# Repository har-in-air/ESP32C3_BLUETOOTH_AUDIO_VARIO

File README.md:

# ESP32C3_BLUETOOTH_AUDIO_VARIO

 * Accurate, zero-lag audio variometer using Kalman filter fusion of accelerometer and pressure sensor data. 
 This project uses the [KF4D kalman filter algorithm](https://github.com/har-in-air/ESP32_IMU_BARO_GPS_VARIO/blob/master/offline/kf/compare_kf2_kf3_kf4.ipynb).

* WiFi Vario configuration via web page.
* Bluetooth LE transmission of [$LK8EX1 sentences](https://github.com/LK8000/LK8000/blob/master/Docs/LK8EX1.txt), to provide apps like [XCTrack](https://xctrack.org/) with 
accurate barometric pressure altitude and climb-rate data.
* Soft-switched power on/off.
* 'No activity' time-out power down  to conserve battery life.
* WiFi Over-the-air (OTA) firmware updates.
* [2-layer PCB layout available, sized for standard Hammond 1551K enclosure](https://github.com/har-in-air/VhARIO-ESPC3).

# Software Build Environment 
* Ubuntu 24.04 LTS AMDx64
* [Visual Studio Code with PlatformIO plugin using Arduino framework](https://randomnerdtutorials.com/vs-code-platformio-ide-esp32-esp8266-arduino/) 
* The file `platformio.ini` specifies the framework packages, toolchain and libraries used by the project. 
* LittleFS partition for hosting HTML web page content.
* Since release v1.20, the software only supports PCB layout revision B.

# Hardware

* AI-Thinker ESP-C3-12F C3FN4 module (4MByte flash, Wi-Fi and Bluetooth LE)
* CJMCU-117 module with MPU9250 9-DOF IMU and MS5611 barometric pressure sensor
* TLV75533 LDO regulator, max current 500mA
* KPEG006 broadband-audio piezo transducer
* 74HC240 used as a push-pull piezo driver for louder volume 
* MCP73871 Li-poly battery charger, max 500mA charging current
* 1800mAHr Lipoly battery
* The USB C interface supports Li-Poly battery charging and program flash/debug.

## Current Drain

With Bluetooth LE disabled, current drain is ~30mA.

With Bluetooth LE enabled and transmitting LK8EX1 messages at 10Hz, current drain is ~85mA.

# Software Build Notes

## Build Steps

* The first time you flash the ESP32-C3 with this project code, select `PROJECT TASKS -> esp32c3 -> Platform -> Erase Flash`. This will wipe the entire flash including any previous partition tables. 
* Next, select `Platform -> Build Filesystem Image`. This will build a LittleFS flash partition with the contents of the `/data` directory. The `/data` directory contains the static HTML and CSS files for the WiFi server webpage.
* Ensure the vario is switched off. 
* Connect the USB cable from your PC to the vario. 
* Press and hold the `PCCA (SW4)` button. 
* Close the jumper or slide-switch (`JP1/SW2)` depending on which part you have installed. 
* Release the `PCCA (SW4)` button. 
* You will see the USB serial/jtag port show up as a new serial port. On Ubuntu it will be `/dev/ttyACMx` instead of `/dev/ttyUSBx`. Set this new port as the upload and monitor port in platformio.ini.
* Next, select `Platform -> Upload Filesystem Image`. This will flash the LittleFS data partition to the ESP32-C3.
* Next, select `General -> Clean All`, then `Build`. This is only required once, to download the source code for the dependent libraries and build them. 
* If the libraries have already been downloaded and compiled, select `General -> Clean` to re-build only the project application code.
* Select `Build` to compile the application firmware binary. 
* Open the jumper/slide switch (`JP1/SW2`) to remove power. 
* Repeat the earlier steps with `PCCA (SW4)` and the jumper/slide switch  (`JP1/SW2`) to set up for flashing the application firmware.
* Select `Upload` to flash the application firmware binary.
* To see  serial debug prints and prompts on boot, open the  jumper/slide switch (`JP1/SW2`) to remove power. 
* Select `Monitor` in Visual Studio Code and then switch on the vario using the `PWR (SW3)` button. Note that the
serial port may change from the one used for upload e.g. from `ttyACM0` to `ttyACM1`.  

* After a full chip erase and firmware upload, there is no calibration data. So you will see a calibration error message. Follow the prompts to calibrate both accelerometer and gyroscope. Once complete, the calibration parameters will be saved to flash.
* [Example startup serial monitor output example after a full flash erase and build.](docs/first_boot_log.txt) 
* Example serial terminal output for normal vario boot (post-caliibration) : 

```
ESP-ROM:esp32c3-api1-20210207
Build:Feb  7 2021
ESP-ROM:esp32c3-api1-20210207
Build:Feb  7 2021
rst:0x15 (USB_UART_CHIP_RESET),boot:0xc (SPI_FAST_FLASH_BOOT)
Saved PC:0x42083766
SPIWP:0xee
mode:DIO, clock div:2
load:0x3fcd5810,len:0x438
load:0x403cc710,len:0x90c
load:0x403ce710,len:0x2624
entry 0x403cc710
E (236) esp_core_dump_flash: No core dump partition found!
E (236) esp_core_dump_flash: No core dump partition found!

ESP32-C3 BLUETOOTH VARIO compiled on Apr  8 2025 at 15:48:49
Firmware Revision 1.01

Load non-volatile configuration and calibration data from flash
WiFi AP credentials
SSID = 
VARIO
climbThresholdCps = 50
zeroThresholdCps = 5
sinkThresholdCps = -250
crossoverCps = 400
KALMAN FILTER
accelVariance = 100
adapt = 100
MISCELLANEOUS
pwrOffTimeoutMinutes = 10
bleEnable = true
Calibration Values
axBias = -390
ayBias = -182
azBias = 234
gxBias = 17
gyBias = -7
gzBias = 22
To start web configuration mode, press and hold the PCC button
until you hear a low-frequency tone. Then release the button
8
7
6
5
4
3
CPU Freq = 80 MHz
XTAL Freq = 40 MHz
APB Freq = 80000000 Hz
Vario mode

Audio indication of battery voltage

Battery voltage = 4.13V
E (4666) ledc: ledc_get_duty(745): LEDC is not initialized

Check communication with MS5611
crcPROM = 0x9, crc calculated = 0x9
MS5611 OK

Check communication with MPU9250
MPU9250 ID = 71, expected 0x71
MPU9250 OK
Counting down to gyro calibration
Press the PCCA button to enforce accelerometer calibration first
10
9
8
7
6
5
4
3
2
1

Calibrating gyro
Num Tries = 1
gxBias = 18
gyBias = -7
gzBias = 22
Gyro calibration OK

MS5611 config
MS5611 Calibration Coeffs : 48939 50595 29263 26380 30963 26826
Tavg : 35C
Pavg : 90986Pa
Zavg : 89864cm

KalmanFilter config
climbToneCps = 50
zeroesToneCps = 5
sinkToneCps = -250
crossoverCps = 400

Bluetooth LE LK8EX1 messages @ 10Hz

```
* The gyroscope is re-calibrated each time on power-up. You should leave the vario un-disturbed (in any orientation) when you hear the count-down beeps for gyroscope calibration. If the vario is disturbed during the gyro calibration process (e.g. you switched the vario on during flight), it will use the last saved gyro calibration parameters.

# WiFi Configuration

To put the vario into WiFi AP server mode, switch on the vario and immediately press and hold the `PCCA (SW4)` button. When you hear a confirmation tone, release the button. 

Connect to the WiFi Access Point `Vario-AP`, no password needed. 

Open the url `http://192.168.4.1` in a browser.
You can use `http://vario.local` with any OS that has mDNS support. MacOS has built-in support. For Ubuntu, install Avahi. For Windows, install Bonjour.

## Configuration Options

### WiFi Credentials
Enter your home WiFi Access Point SSID and password so that the vario can connect to the access point as a station. Then you can just enter the webpage url `http://vario.local` to access the vario configuration web page.

If the external Access Point is not configured or the configured access point is not available, e.g. on the launch site, the vario will configure itself as a standalone Wifi Access Point with SSID `Vario-AP`, no password. You can use your phone or tablet to connect first to this access point. Then access the webpage url `http://vario.local` as before.

### Audio Tone configuration

The climb tone threshold should be configured for what you consider the minimum climbrate that you can turn in without losing height. The range is +20cm/s to +100cm/s.

Since a paraglider has a 'hands-up' sink rate of approximately -1m/s in still air, anything more than this indicates rising air. 
The zero tone is used to indicate air that is rising, but not strong enough for aggressive turns. The range is -20cm/s to +20cm/s. 

The sink tone is used to indicate sinking air, not a sinking glider. The range is -400cm/s to -100cm/s.

Note that these thresholds are purely personal choices, depending on how 'talkative' you want the vario to be.

The crossover climbrate is used to adjust the frequency discrimination. The vario allocates 3 octaves of audio bandwidth to climbrates below this threshold, and 1 octave
above the threshold. So if the expected average thermal strength is +5m/s, set the threshold to 500.

### Kalman Filter configuration
Set the `variance` parameter lower for conditions with soft, wide and smooth-edged thermals. Set the parameter higher for conditions with strong, narrow and hard-edged thermals.

The `adapt` parameter will probably be removed after flight trials. Higher values add more uncertainty into the Kalman filter so it can respond to high acceleration transitions quickly, while maintaining a high degree of damping in zero acceleration conditions.

### Inactivity Time-out
The vario will power off automatically to save battery life if it does not detect climb/sink rates beyond a minimum threshold within a specified interval (specified in minutes). If you often stand on the launch site for several minutes, hooked-up to the glider and waiting for launch conditions to improve, use a larger time-out.

### Bluetooth LK8EX1
If you enable this option, the vario will transmit $LK8EX1 sentences using the Bluetooth LE protocol at 10Hz. The Bluetooth device name is `BLE-Vario`.

`XCDisplay` app on Apple iPhone connected to the vario, displaying pressure altitude and climbrate.

# Usage

## Power On 
To power on, press the `PWR (SW3)` button and hold (~1 second) until you see the power/bluetooth LED turn on. Release.

The vario will first indicate the battery charge status with a series of long beeps. 5 beeps for fully charged, 1 beep for discharged.

After a pause, the vario will indicate the countdown to gyro calibration with a series of 10 shorter beeps. You should ensure the vario is left undisturbed, in any orientation (do not hold it in your hand). At the end of the countdown and a brief pause, you may hear an initial squawk as the filter initializes, but it should settle down in a few seconds. Now the vario is operational and providing audio feedback.

If you want to force accelerometer re-calibration, press the `PCCA (SW4)` button during the gyro calibration countdown. Now the vario will start a 50 short beep countdown at a fast rate. At this point you should place the vario flat on a horizontal surface (confirm with a bubble level if possible) without any disturbance, vibrations etc. Do not hold or press down on the vario case. At the end of the 50 beeps, the accelerometer will be calibrated, and then the countdown to gyro calibration will start.

### Power/Bluetooth LED
If Bluetooth transmission is disabled, the power/bluetooth LED will stay on.

If Bluetooth transmission is enabled, the power/bluetooth LED will start blinking once every 2 seconds after transmission starts.

### Audio Mute 
When the vario has finished initialization and is providing vario audio feedback, a brief press of the `PCCA (SW4)` button  will toggle the audio on / off.

This is convenient if you have set the zero-tone threshold to a negative value or close to zero and don't want the distraction of a beeping vario while you are hooked in to the glider and waiting to launch.

## Power Off
To power off, press the `PWR (SW3)` button and hold (~2 seconds) until you hear a confirmation audio tone. If the power/bluetooth LED was on, it will turn off as well. Release.

# Notes on Calibration and Use
The accelerometer offset calibration with the vario in a horizontal position needs to be done AFTER the board is installed in the case and BEFORE first use.

Gyro offset calibration is done on each power up. For that the only requirement is that the unit should not be disturbed, it can be in any orientation.  If it is disturbed, it will use the previous saved gyro offsets. This will not be an issue  if you successfully calibrated the gyro in the past few days and are flying in similar temperature conditions.

After offset calibration and in normal use the AHRS software computes the vario orientation in Earth coordinates and then the 
net acceleration along the Earth coordinates +Z axis, every 2mS. This is NOT the IMU chip z axis acceleration. 

So the vario does not have to be horizontal during use, you can mount it to your waist strap or riser.

You will need to redo the accelerometer offset calibration if you have reinstalled the board in the case, or tightened/loosened the mounting screws. The stress from the mounting screws will translate to stress on the MEMS structures in the IMU chip soldered to the module board, which will change the axis offsets. 

My friend who mounted the module board with a standard 0.1in header to the main PCB had very large accelerometer offsets. I was concerned that he had a defective MPU9250 chip. He reinstalled the IMU module board with double-sided foam tape and thin flexible wires, and then the offsets on all axes were very low.

The accelerometer calibration will remove the offsets, but it's good to remove external contributing factors, especially if the offset is so large that it affects the dynamic range. 

# Credits

Prototype design, component sourcing, PCB assembly and testing in collaboration with Benoit Arnal.

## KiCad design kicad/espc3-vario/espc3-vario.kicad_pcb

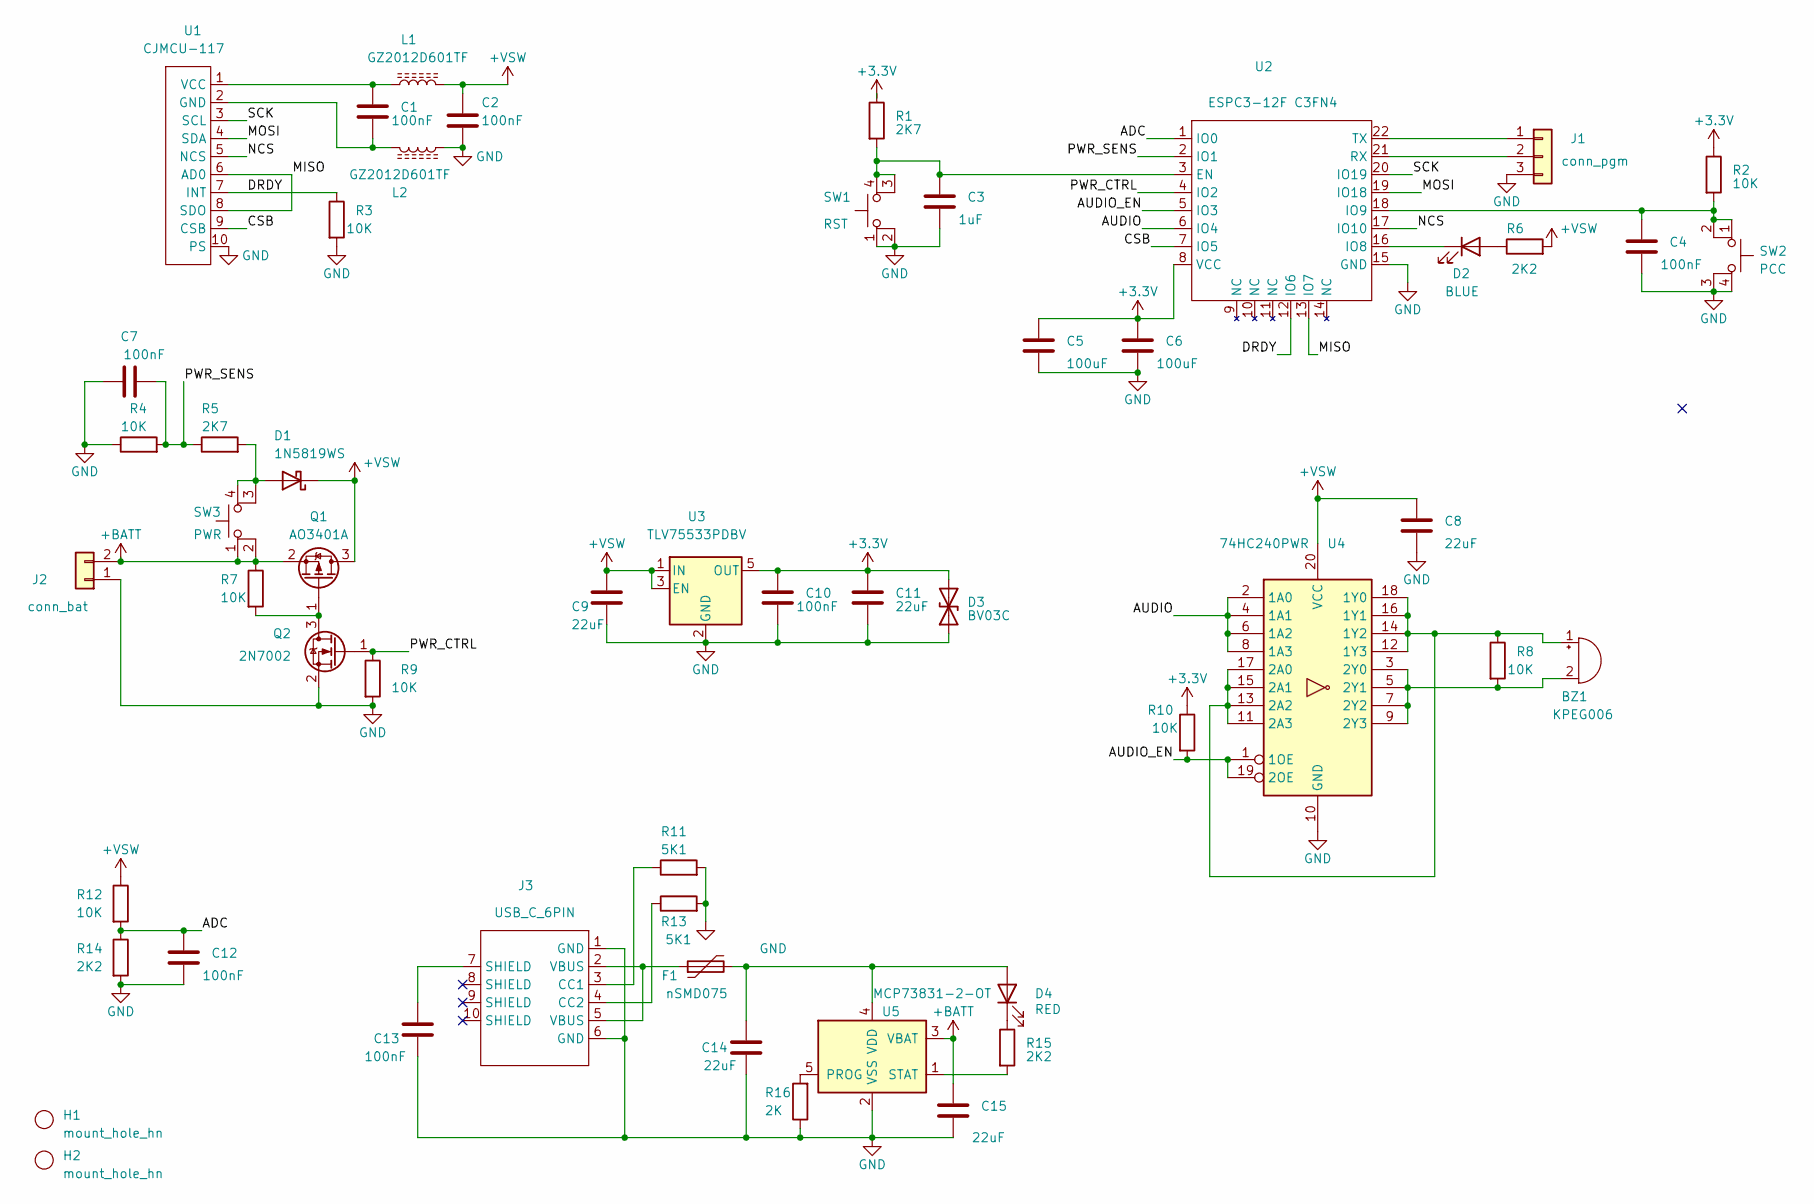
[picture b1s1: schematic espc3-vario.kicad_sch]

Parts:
BZ1: KPEG006; smd_conn2_hn
C1, C2, C4, C7, C10, C12, C13: 100nF; C_0805_2012Metric_Pad1.18x1.45mm_HandSolder
C3: 1uF; C_0805_2012Metric_Pad1.18x1.45mm_HandSolder
C5, C6: 100uF; C_1206_3216Metric_Pad1.33x1.80mm_HandSolder
C8, C9, C11, C14, C15: 22uF; C_1206_3216Metric_Pad1.33x1.80mm_HandSolder
D1: 1N5819WS; D_SOD-323_HandSoldering
D2: BLUE; LED_0805_2012Metric_Pad1.15x1.40mm_HandSolder
D3: BV03C; D_SOD-323_HandSoldering
D4: RED; LED_0805_2012Metric_Pad1.15x1.40mm_HandSolder
F1: nSMD075; Fuse_1206_3216Metric_Pad1.42x1.75mm_HandSolder
H1, H2: mount_hole_hn; MountingHole_2.5mm
J1: conn_pgm; pgm_conn_hn
J2: conn_bat; smd_conn2_hn
J3: USB_C_6PIN; usbc_6pin_hn
L1, L2: GZ2012D601TF; L_0805_2012Metric_Pad1.15x1.40mm_HandSolder
Q1: AO3401A; SOT-23_Handsoldering
Q2: 2N7002; SOT-23_Handsoldering
R1, R5: 2K7; R_0805_2012Metric_Pad1.20x1.40mm_HandSolder
R2, R3, R4, R7, R8, R9, R10, R12: 10K; R_0805_2012Metric_Pad1.20x1.40mm_HandSolder
R6, R14, R15: 2K2; R_0805_2012Metric_Pad1.20x1.40mm_HandSolder
R11, R13: 5K1; R_0805_2012Metric_Pad1.20x1.40mm_HandSolder
R16: 2K; R_0805_2012Metric_Pad1.20x1.40mm_HandSolder
SW1: RST; smd_btn4_hn
SW2: PCC; smd_btn4_hn
SW3: PWR; smd_btn4_hn
U1: CJMCU-117; cjmcu_117_hn
U2: ESPC3-12F C3FN4; espc3fn4_hn
U3: TLV75533PDBV; SOT-23-5_HandSoldering
U4: 74HC240PWR; SSOP-20_4.4x6.5mm_P0.65mm
U5: MCP73831-2-OT; SOT-23-5_HandSoldering

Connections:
+3V3: C5.1, C6.1, C10.1, C11.1, D3.2 (A2), R1.1, R2.1, R10.1, U2.8 (VCC), U3.5 (OUT)
+BATT: C15.1, J2.2, Q1.2 (S), R7.1, SW3.1, SW3.2, U5.3 (VBAT)
+VSW: C2.1, C8.1, C9.1, D1.1 (K), L1.2, Q1.3 (D), R6.2, R12.1, U3.1 (IN), U3.3 (EN), U4.20 (VCC)
/ADC: C12.1, R12.2, R14.1, U2.1 (IO0)
/AUDIO: U2.6 (IO4), U4.2 (1A0), U4.4 (1A1), U4.6 (1A2), U4.8 (1A3)
/AUDIO_EN: R10.2, U2.5 (IO3), U4.1 (1OE), U4.19 (2OE)
/CSB: U1.9 (CSB), U2.7 (IO5)
/DRDY: R3.1, U1.7 (INT), U2.12 (IO6)
/MISO: U1.6 (AD0), U1.8 (SDO), U2.13 (IO7)
/MOSI: U1.4 (SDA), U2.19 (IO18)
/NCS: U1.5 (NCS), U2.17 (IO10)
/PWR_CTRL: Q2.1 (G), R9.1, U2.4 (IO2)
/PWR_SENS: C7.2, R4.2, R5.1, U2.2 (IO1)
/SCK: U1.3 (SCL), U2.20 (IO19)
GND: C2.2, C3.2, C4.2, C5.2, C6.2, C7.1, C8.2, C9.2, C10.2, C11.2, C12.2, C13.2, C14.2, C15.2, D3.1 (A1), J1.3, J2.1, J3.1 (GND), J3.6 (GND), L2.1, Q2.2 (S), R3.2, R4.1, R9.2, R11.2, R13.2, R14.2, R16.1, SW1.1, SW1.2, SW2.3 (K), SW2.4 (A), U1.10 (PS), U2.15 (GND), U3.2 (GND), U4.10 (GND), U5.2 (VSS)
unnamed: BZ1.2 (+), R8.2, U4.3 (2Y0), U4.5 (2Y1), U4.7 (2Y2), U4.9 (2Y3)
unnamed: BZ1.1 (-), R8.1, U4.11 (2A3), U4.12 (1Y3), U4.13 (2A2), U4.14 (1Y2), U4.15 (2A1), U4.16 (1Y1), U4.17 (2A0), U4.18 (1Y0)
unnamed: D1.2 (A), R5.2, SW3.3 (K), SW3.4 (A)
unnamed: D2.2 (A), R6.1
unnamed: D2.1 (K), U2.16 (IO8)
unnamed: C14.1, D4.2 (A), F1.2, U5.4 (VDD)
unnamed: D4.1 (K), R15.1
unnamed: J1.1, U2.22 (TX)
unnamed: J1.2, U2.21 (RX)
unnamed: J3.3 (CC1), R11.1
unnamed: J3.4 (CC2), R13.1
unnamed: C13.1, J3.7 (SHIELD)
unnamed: F1.1, J3.2 (VBUS), J3.5 (VBUS)
unnamed: Q1.1 (G), Q2.3 (D), R7.2
unnamed: C3.1, R1.2, SW1.3 (K), SW1.4 (A), U2.3 (EN)
unnamed: C1.2, L2.2, U1.2 (GND)
unnamed: C1.1, L1.1, U1.1 (VCC)
unnamed: C4.1, R2.2, SW2.1, SW2.2, U2.18 (IO9)
unnamed: R16.2, U5.5 (PROG)
unnamed: R15.2, U5.1 (STAT)

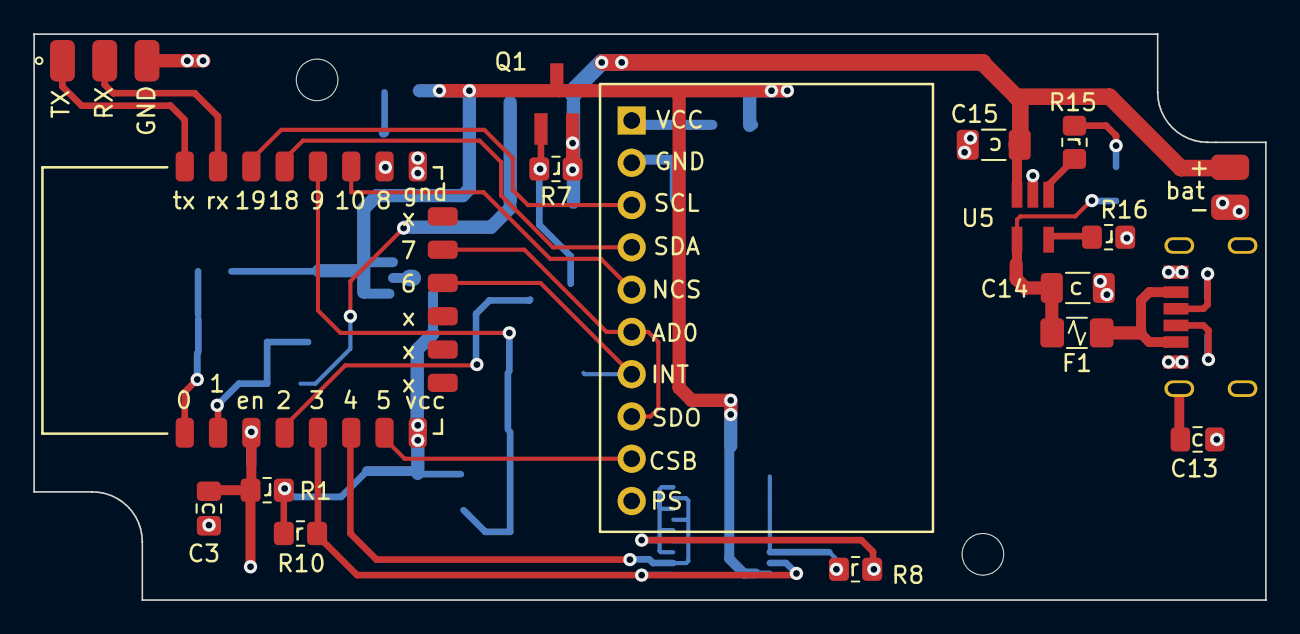
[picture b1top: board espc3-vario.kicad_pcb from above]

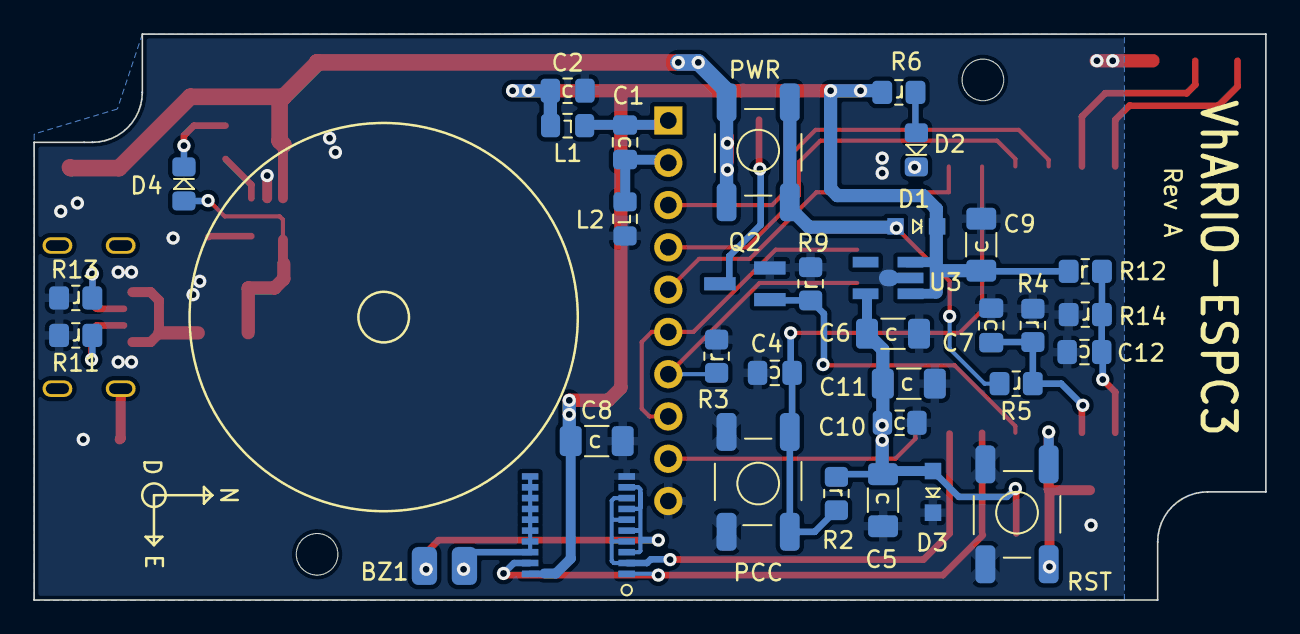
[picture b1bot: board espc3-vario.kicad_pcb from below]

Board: 2 copper layers, 74.0 x 34.0 mm, 54 parts (34 on the bottom side), 35 nets.

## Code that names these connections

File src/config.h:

#ifndef CONFIG_H_
#define CONFIG_H_


#define pinPCCA		9	// program/configure/calibrate/audio button
#define pinAudio	7	// pwm beeper audio output
#define pinAudioEn	6	// 74HC240 output enables, active low

#define pinPwrSens	21	// detect power on/off button press
#define pinPwrCtrl	10	// power on/off

#define pinCSB		20	// CSB (ms5611)
#define pinMISO		1	// SDO ms5611 & AD0 mpu9250
#define pinNCS		3 	// NCS (mpu9250)
#define pinMOSI		4 	// SDA
#define pinSCK		5	// SCL
#define pinDRDYInt	2  	// INT
#define pinLED		8	// power-on and bluetooth active indication


#define BTN_PCCA()  (digitalRead(pinPCCA) == HIGH ? 1 : 0)

#define LED_ON() 	{digitalWrite(pinLED, 0); LEDState = 1;}
#define LED_OFF() 	{digitalWrite(pinLED, 1); LEDState = 0;}

#define PWR_ON_DELAY_MS		1000UL
#define PWR_OFF_DELAY_MS	2000UL

////////////////////////////////////////////////////////////////////
// WEB CONFIGURATION PARAMETER DEFAULTS AND LIMITS

// vario thresholds in cm/sec for generating different
// audio tones. Between the sink threshold and the zero threshold,
// the vario is quiet

#define VARIO_CLIMB_THRESHOLD_CPS_DEFAULT  	50
#define VARIO_CLIMB_THRESHOLD_CPS_MIN   	20
#define VARIO_CLIMB_THRESHOLD_CPS_MAX   	100

#define VARIO_ZERO_THRESHOLD_CPS_DEFAULT  	5
#define VARIO_ZERO_THRESHOLD_CPS_MIN    	-20
#define VARIO_ZERO_THRESHOLD_CPS_MAX    	20

#define VARIO_SINK_THRESHOLD_CPS_DEFAULT  	-250
#define VARIO_SINK_THRESHOLD_CPS_MIN    	-400
#define VARIO_SINK_THRESHOLD_CPS_MAX    	-100

// When generating climbtones, the vario allocates most of the speaker 
// frequency bandwidth to climbrates below this crossover threshold 
// so you have more frequency discrimination. So set the crossover threshold 
// to the average thermal core climbrate you expect for the site and conditions.
#define VARIO_CROSSOVER_CPS_DEFAULT     400
#define VARIO_CROSSOVER_CPS_MIN         300
#define VARIO_CROSSOVER_CPS_MAX         600

// Kalman filter configuration
#define KF_ACCEL_VARIANCE_DEFAULT     100
#define KF_ACCEL_VARIANCE_MIN         50
#define KF_ACCEL_VARIANCE_MAX         150

#define KF_ADAPT_DEFAULT	100
#define KF_ADAPT_MIN		50
#define KF_ADAPT_MAX		150

// Power-off timeout. The vario will power down
// if it does not detect climb or sink rates more than
// PWR_OFF_THRESHOLD_CPS, for the specified minutes.
#define PWR_OFF_TIMEOUT_MINUTES_DEFAULT   10
#define PWR_OFF_TIMEOUT_MINUTES_MIN       5
#define PWR_OFF_TIMEOUT_MINUTES_MAX       20

// audio feedback tones
#define BATTERY_TONE_HZ			400
#define CALIBRATING_TONE_HZ		800
#define UNCALIBRATED_TONE_HZ	2000
#define MPU9250_ERROR_TONE_HZ	200 
#define MS5611_ERROR_TONE_HZ	2500

// BLE LK8EX1 transmission is enabled as default
#define BLE_DEFAULT  true

////////////////////////////////////////////////////////////////////////////////
// COMPILED CONFIGURATION PARAMETERS ( cannot be changed with web configuration )

//#define USE_9DOF_AHRS

#define PWR_CTRL_TASK_PRIORITY	2
#define BLE_TASK_PRIORITY		3
#define WIFI_CFG_TASK_PRIORITY	3
#define VARIO_TASK_PRIORITY		(configMAX_PRIORITIES-2)

// change these parameters based on the frequency bandwidth of the speaker
#define VARIO_SPKR_MIN_FREQHZ      	200
#define VARIO_SPKR_MAX_FREQHZ       3200

// three octaves (2:1) of frequency for climbrates below crossoverCps,
// and one octave of frequency for climbrates above crossoverCps.
// This gives you more perceived frequency discrimination for climbrates 
// below crossoverCps
#define VARIO_CROSSOVER_FREQHZ    	1600

#define KF_ADAPT         1.0f

// Acceleration bias uncertainty is set low as the residual acceleration bias 
// (post-calibration) is expected to have low variation/drift. It is further reduced
// depending on the acceleration magnitude, as we want the acceleration bias estimate 
// to evolve ideally in a zero acceleration environment.
#define KF_ACCELBIAS_VARIANCE   	0.005f

// KF4 Acceleration Measurement Noise variance
#define KF_A_MEAS_VARIANCE   		10.0f

// KF4 Altitude Measurement Noise Variance
#define KF_Z_MEAS_VARIANCE			200.0f

// If climbrate or sinkrate stays below this threshold for the configured
// time interval, vario goes to sleep to conserve power
#define PWR_OFF_THRESHOLD_CPS    	50

// if you find that gyro calibration fails even when you leave
// the unit undisturbed, increase this offset limit
// until you find that gyro calibration works consistently.
#define GYRO_OFFSET_LIMIT_1000DPS   200

// print debug information to the serial port for different code modules
// For revB hardware, after flashing the code and validating the calibration parameters look reasonable,
// ensure this is commented out
#define TOP_DEBUG
#ifdef TOP_DEBUG
	#define dbg_println(x) {Serial.println x;}
	#define dbg_printf(x)  {Serial.printf x;}
	#define dbg_flush()  Serial.flush()
#else
	#define dbg_println(x)
	#define dbg_printf(x)
	#define dbg_flush()
#endif
// these #defines can be left uncommented after debugging, as the enclosed
// debug prints do not appear in the critical run-time loop
#define KF_DEBUG
#define VARIO_DEBUG
#define NVD_DEBUG
#define MPU9250_DEBUG
#define MS5611_DEBUG
#define WEBCFG_DEBUG

// !! ensure these #defines are commented out after debugging, as the 
// enclosed debug prints are in the critical run-time loop.
//#define IMU_DEBUG
//#define PERF_DEBUG
//#define BLE_DEBUG

#endif

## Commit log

2022-01-26 reduce tx power
2022-03-11 SPI interface, Kicad schematic and layout
2022-03-11 update schematic pdf
2022-03-11 remove kicad subdirectory
2022-03-21 kf4 update
2022-03-23 compile support 9DOF/6DOF, audio mute, adapt coef
2022-03-30 cleanup, tweak config params
2022-03-30 clean up
2022-03-31 tweak config params
2022-04-03 update docs
2022-05-06 use ota partitions, update platformio.ini
2022-05-07 tweak variances
2022-05-07 calib adc, modify kf4, bt led 1hz
2022-05-07 kf tweaks
2022-05-09 cleanup, use partitions.csv
2022-05-10 tweak kf
2022-05-10 sliders
2022-05-10 tweak slider
2022-05-10 change timeout imits
2022-05-10 tweak config sliders
2022-05-11 tweak webpage
2022-05-12 make kf adapt compile param
2022-05-12 webpage button resize
2022-05-13 use esp32-c3-devkitm-1 env
2022-05-13 update platformio doc link
2022-05-15 revert to kf adapt as user param
2022-05-15 revert platformio.ini
2022-05-15 power off tone changed
2022-05-18 udpate readme
2022-06-29 support Rev B hardware
2022-08-09 power off delay, revA/B
2022-08-14 fix hw rev b
2022-08-14 remove mklittlefs
2022-08-14 remove littlefsbuilder.py
2022-08-14 mod partitions
2022-08-14 change flash freq
2022-09-11 no usb cdc on boot, 40mhz flash
2022-09-12 change ble tx power
2023-12-13 clean platformio.ini, change task priorities
2024-05-14 Create LICENSE
2024-09-15 Create Issue Branch
2024-09-15 Commented AsyncElegantOTA to make it compile
2024-09-15 Remove hardware revisions (fix to B) and add esp32 environment
2024-09-15 Move common settings to env section
    and define USBSerial in config.h again as in platform.ini it does not seem to work...
2024-09-21 Removed fixed serial ports
2024-09-21 Added pin definition for normal ESP32
2024-09-21 audio_init() which takes care of attachPin and more
    Introduced PWR_CTRL
2024-09-21 Disable sensors if not defined SPI_SENSORS
    moved spi init
2024-09-21 Send every gps sentence on ble
2024-09-21 Just pass thru "$GPRMC" and "$GPGGA"
2024-09-22 Increase gpsSentence[] size to 160
    as sentences turns out to be 73 long
2024-09-22 Add simulated values in case of no SPI_SENSORS
    And pull down on interrupt pin to prevent spurious interrupts if no sensors are connected
2024-09-22 Refactored audio
    Internalized on(0 and off().
2024-09-22 Use refactored audio
2024-09-23 Refactored adc/battery code
2024-09-23 Send percentage via BLE
2024-10-01 Reshuffle pins for C3
2024-10-01 Decrease waiting times during startup
2024-10-01 Add printing of MS5611 prom contents
2024-10-01 Allow device id 0x70 for MPU9250 when not USE_9DOF_AHRS
2024-10-01 Switch audio on and of in audio_set_frequency()
    Does not seem to impact performance or audibility
2024-10-01 Improved PWR_CTRL and added GPS_CONNECTED
2024-10-02 Added Serial Studio output in case ALTI_DEBUG is defined
2024-10-02 Some pin swapping
2024-10-07 Use RX for GPS only
2024-10-07 Add AUX_SERIAL
2024-10-10 Duty cycle to 0x1FF for 10 bit LEDC
    And do not disable/enable audio pin twice
2024-10-10 Change Wifi name to Bavario
2024-10-10 Limit BLE packet size to 20 bytes
2025-04-05 fix compile errors for latest libraries
2025-04-07 change ledc* api to be compatible with arduino 2.x used by platformio
2025-04-08 update README, fw version no
2025-04-24 only support pcb layout rev B
2025-04-25 freeze dependent library versions
2025-04-25 update release info
